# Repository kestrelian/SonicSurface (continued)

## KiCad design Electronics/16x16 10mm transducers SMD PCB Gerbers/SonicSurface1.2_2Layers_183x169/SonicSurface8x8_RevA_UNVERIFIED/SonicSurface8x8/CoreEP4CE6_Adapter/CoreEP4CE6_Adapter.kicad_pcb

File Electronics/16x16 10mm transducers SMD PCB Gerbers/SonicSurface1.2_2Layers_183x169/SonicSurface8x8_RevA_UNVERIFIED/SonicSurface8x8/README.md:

# SonicSurface 8x8 - Rev A

Local engineering design package, 22 October 2026. **UNVERIFIED: NOT RELEASED FOR FABRICATION.**

This is a new circuit and PCB implementation informed by the supplied SonicSurface manufacturing files. Gerbers do not preserve an editable schematic or authoritative circuit netlist. This package is not a recovered original KiCad project.

## Open in KiCad 10

- `Array8x8/Array8x8.kicad_pro`: 160 x 124 mm, two-layer array PCB; root schematic and eight row sheets.
- `CoreEP4CE6_Adapter/CoreEP4CE6_Adapter.kicad_pro`: 38 x 65 mm, two-layer plug-in P1-to-IDC26 cable adapter.
- Each project contains its own symbols, footprints and library tables.
- Each `fabrication_UNVERIFIED/` directory contains Gerber and Excellon exports. Do not send these to a manufacturer until the deferred checks pass.
- `schematic_svg/` contains readable schematic exports; `BOM.csv` lists components individually; `connectivity.csv` records intended pin-to-net assignments.
- `CABLE_PIN_MAP.csv` and `CoreEP4CE6_8x8_pins.qsf` define the module interface. `CHANNEL_MAP.csv` supplies all 64 physical and acoustic coordinates.
- `DESIGN_NOTES.md`, `ASSEMBLY.md`, and `QA_CHECKLIST.md` explain design assumptions, assembly, and deferred verification.

## Implemented parts

64 Murata MA40S4S; 32 Microchip TC4427EPA DIP-8; 8 74HC595N DIP-16. The driver package supersedes the earlier SOIC suggestion. The CoreEP4CE6 is external and connects through a straight 26-way ribbon and the adapter. No bare FPGA is fitted to the array.

The transducer pitch is **12 mm**, enlarged from the original approximately 10.5 mm to make room for DIP through-hole pads. The active grid spans 84 mm between the first and last centres. The transducer body envelope is about 94.2 x 94.2 mm at maximum body diameter. Array board area is about 35.8% smaller than the supplied 183 x 169 mm board.

## Completion and verification are separate

The package contains native editable design files and manufacturing exports. Routing generation status is recorded in each project's `routing_status.json`; that is an authoring log, **not** a connectivity, clearance, signal integrity or manufacturing test result. The array has routed ground connections supplemented by copper pours; the adapter has ground pours and stitching vias. The final checklist is intentionally unexecuted at the user's request. Physical fit, all-net connectivity, component ratings under actual operation, cable timing, and acoustic performance remain unverified.

No FPGA bitstream is supplied. The QSF is a pin-assignment fragment, not a complete Quartus project. Firmware adaptation and compilation are needed before use. The old 256-channel bitstream must not be used unchanged.

Everything remains local. Nothing has been committed, pushed, uploaded to a PCB service, or ordered.

## Reproduction

Use the Python supplied with KiCad 10. `build_design.py` regenerates placed boards and schematics, **overwriting edits in the generated project files**. Do not rebuild over manual work; copy the package first.

For the array, `prepare_router_input.py` produces a Specctra DSN with explicit 0.25 mm signal / 0.8 mm power / 0.4 mm ground rules. Route that DSN with Freerouting 2.5.0 Java locally, then run `import_array_routing.py` to import `authoring/routed.ses` and add ground pours. The session is included, so it can be re-imported without rerunning the router. `route_design.py CoreEP4CE6_Adapter` reproduces the adapter's grid routing. The grid router is retained for provenance but did not complete the array routing; do not replace the array with that intermediate result. `export_fabrication.py` writes Gerbers/drills from the native boards.

No script in this package runs the final QA checklist. The native Freerouting executable was blocked by Windows; the official Java distribution was used with a portable Temurin 25 runtime instead. Downloads and router runtime files are local under `tools/` but are excluded from the delivery ZIP. No Windows security setting was changed. The official tool and runtime can be obtained from [Freerouting releases](https://github.com/freerouting/freerouting/releases/tag/v2.5.0) and [Eclipse Adoptium](https://adoptium.net/).

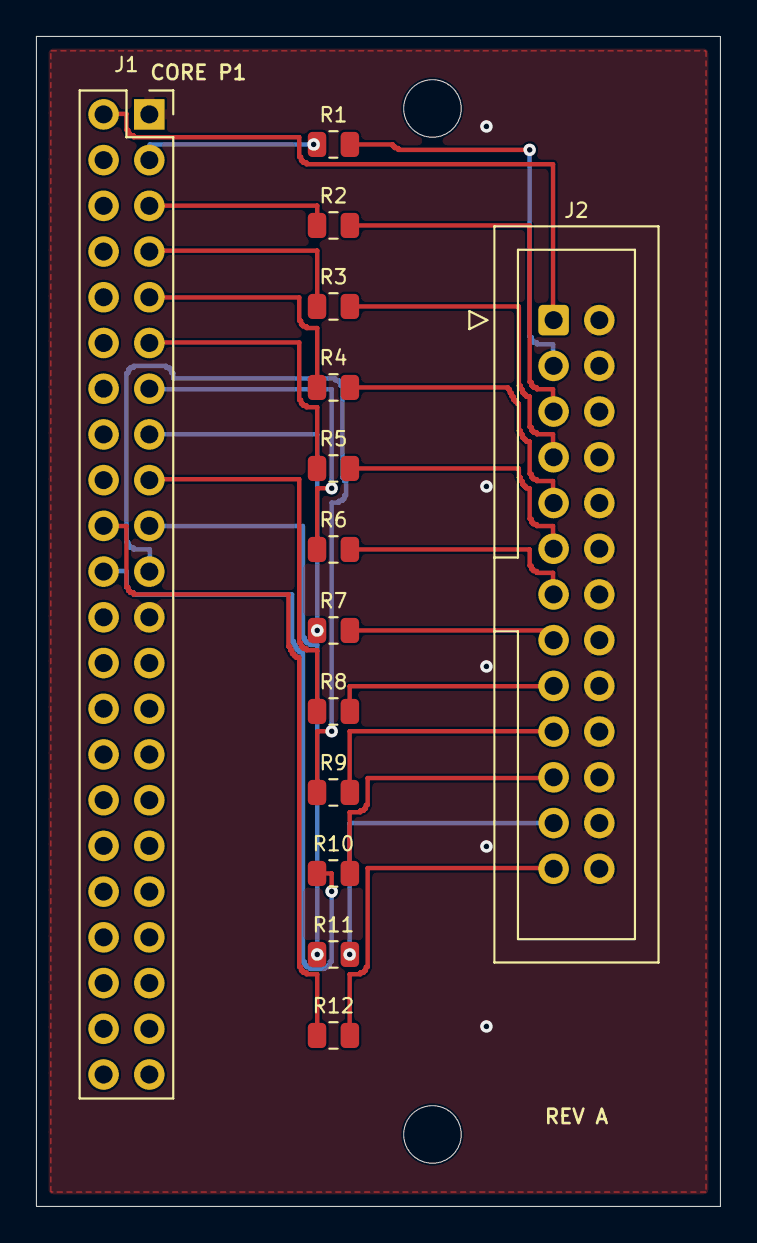
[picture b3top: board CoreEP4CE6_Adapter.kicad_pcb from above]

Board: 2 copper layers, 38.0 x 65.0 mm, 16 parts (0 on the bottom side), 26 nets.

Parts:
H1, H2: MountingHole_3.2mm_M3
J1: CoreEP4CE6 P1 ONLY; PinSocket_2x22_P2.54mm_Vertical
J2: IDC26 to ARRAY J1; IDC-Header_2x13_P2.54mm_Vertical
R1, R2, R3, R4, R5, R6, R7, R8, R9, R10, R11, R12: 33R source termination; R_0805_2012Metric

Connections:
+3V3: J1.2, J2.1
CLR_N: J2.25, R12.2
CLR_N_SRC: J1.20, R12.1
DATA0: J2.3, R1.2
DATA0_SRC: J1.3, R1.1
DATA1: J2.5, R2.2
DATA1_SRC: J1.5, R2.1
DATA2: J2.7, R3.2
DATA2_SRC: J1.7, R3.1
DATA3: J2.9, R4.2
DATA3_SRC: J1.9, R4.1
DATA4: J2.11, R5.2
DATA4_SRC: J1.11, R5.1
DATA5: J2.13, R6.2
DATA5_SRC: J1.13, R6.1
DATA6: J2.15, R7.2
DATA6_SRC: J1.15, R7.1
DATA7: J2.17, R8.2
DATA7_SRC: J1.17, R8.1
GND: J1.1, J1.23, J2.2, J2.4, J2.6, J2.8, J2.10, J2.12, J2.14, J2.16, J2.18, J2.20, J2.22, J2.24, J2.26
LATCH: J2.21, R10.2
LATCH_SRC: J1.22, R10.1
OE_N: J2.23, R11.2
OE_N_SRC: J1.19, R11.1
SCLK: J2.19, R9.2
SCLK_SRC: J1.21, R9.1

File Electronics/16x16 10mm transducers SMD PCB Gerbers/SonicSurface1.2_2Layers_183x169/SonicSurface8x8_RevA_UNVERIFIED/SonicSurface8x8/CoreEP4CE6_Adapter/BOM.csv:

Reference,Value / part,Footprint,Quantity,Notes
J1,CoreEP4CE6 P1 ONLY,SS8:PinSocket_2x22_P2.54mm_Vertical,1,Unverified Rev A
J2,IDC26 to ARRAY J1,SS8:IDC-Header_2x13_P2.54mm_Vertical,1,Unverified Rev A
R1,33R source termination,SS8:R_0805_2012Metric,1,Unverified Rev A
R2,33R source termination,SS8:R_0805_2012Metric,1,Unverified Rev A
R3,33R source termination,SS8:R_0805_2012Metric,1,Unverified Rev A
R4,33R source termination,SS8:R_0805_2012Metric,1,Unverified Rev A
R5,33R source termination,SS8:R_0805_2012Metric,1,Unverified Rev A
R6,33R source termination,SS8:R_0805_2012Metric,1,Unverified Rev A
R7,33R source termination,SS8:R_0805_2012Metric,1,Unverified Rev A
R8,33R source termination,SS8:R_0805_2012Metric,1,Unverified Rev A
R9,33R source termination,SS8:R_0805_2012Metric,1,Unverified Rev A
R10,33R source termination,SS8:R_0805_2012Metric,1,Unverified Rev A
R11,33R source termination,SS8:R_0805_2012Metric,1,Unverified Rev A
R12,33R source termination,SS8:R_0805_2012Metric,1,Unverified Rev A

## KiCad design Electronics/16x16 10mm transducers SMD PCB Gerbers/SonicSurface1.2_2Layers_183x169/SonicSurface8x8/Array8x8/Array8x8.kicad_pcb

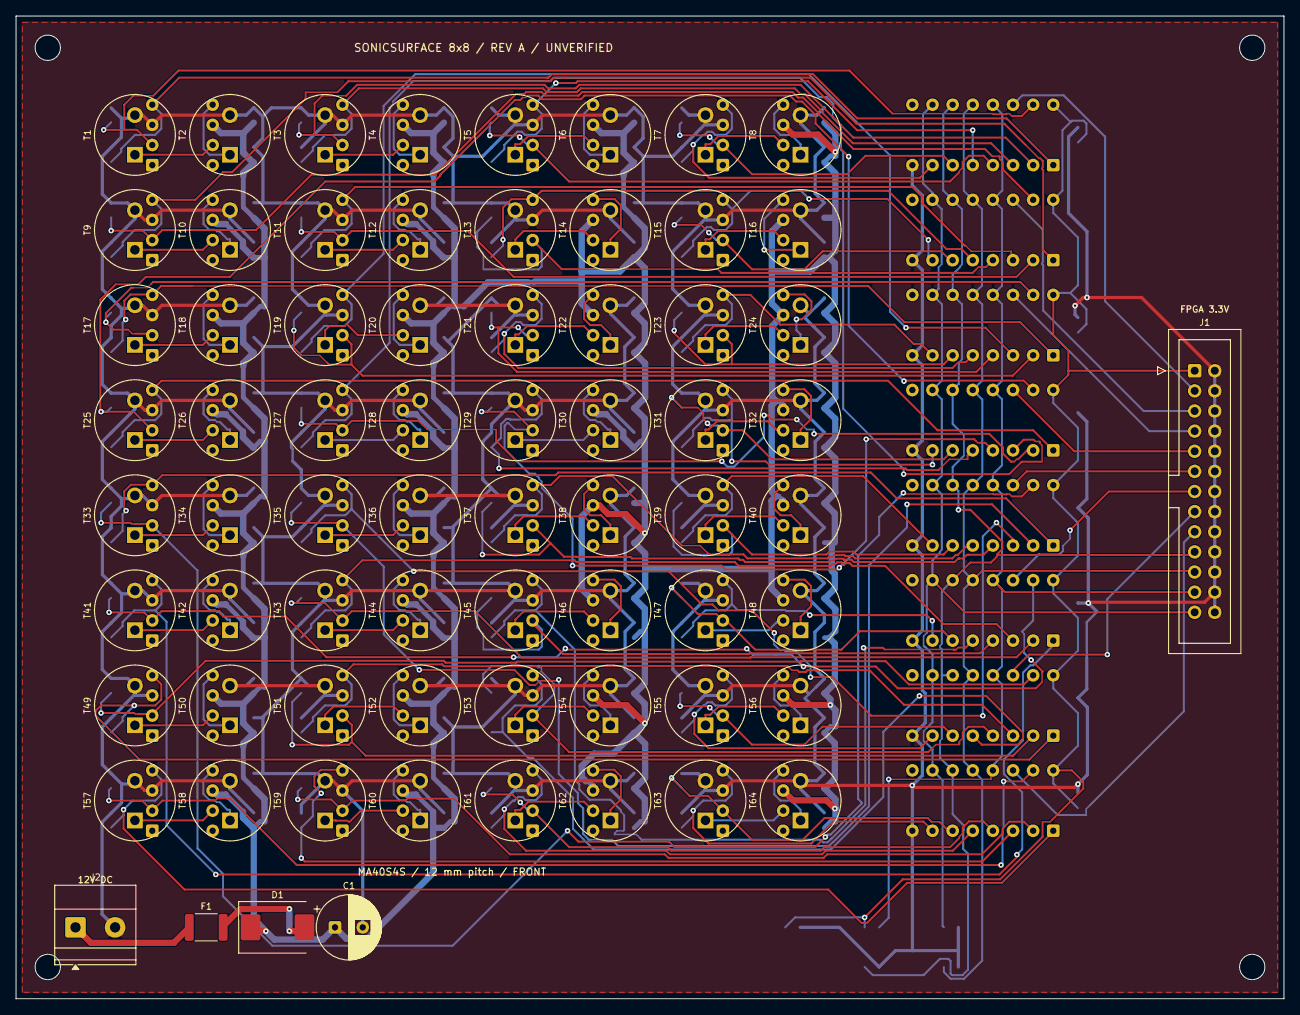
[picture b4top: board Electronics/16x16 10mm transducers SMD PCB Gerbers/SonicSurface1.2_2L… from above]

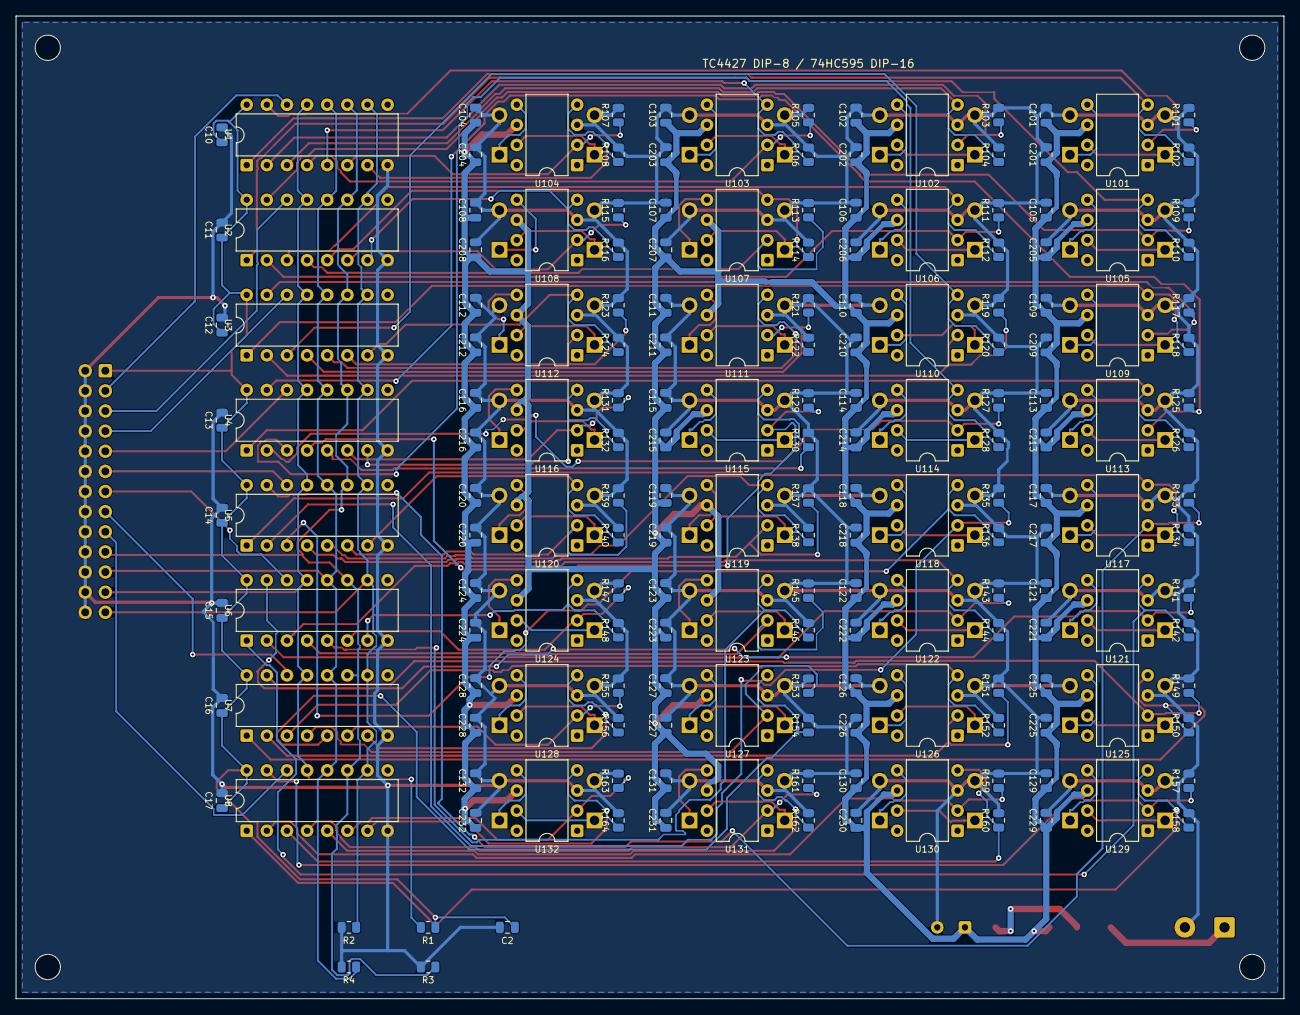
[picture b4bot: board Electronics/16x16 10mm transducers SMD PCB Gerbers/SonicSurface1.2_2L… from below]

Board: 2 copper layers, 160.0 x 124.0 mm, 254 parts (181 on the bottom side), 145 nets.

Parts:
C1: 220uF 35V low ESR; CP_Radial_D8.0mm_P3.50mm
C2: 10uF 10V X7R; C_0805_2012Metric
C10, C11, C12, C13, C14, C15, C16, C17, C101, C102, C103, C104, C105, C106, C107, C108, C109, C110, C111, C112, C113, C114, C115, C116, C117, C118, C119, C120, C121, C122, C123, C124, C125, C126, C127, C128, C129, C130, C131, C132: 100nF 50V X7R; C_0805_2012Metric
C201, C202, C203, C204, C205, C206, C207, C208, C209, C210, C211, C212, C213, C214, C215, C216, C217, C218, C219, C220, C221, C222, C223, C224, C225, C226, C227, C228, C229, C230, C231, C232: 1uF 50V X7R; C_0805_2012Metric
D1: SS34 / SMC; D_SMC
F1: 1A fast / 1812; Fuse_1812_4532Metric
H1, H2, H3, H4: MountingHole_3.2mm_M3
J1: IDC26 / FPGA CABLE; IDC-Header_2x13_P2.54mm_Vertical
J2: 12V DC INPUT; TerminalBlock_Phoenix_MKDS-1,5-2_1x02_P5.00mm_Horizontal
R1, R2, R3, R4, R101, R102, R103, R104, R105, R106, R107, R108, R109, R110, R111, R112, R113, R114, R115, R116, R117, R118, R119, R120, R121, R122, R123, R124, R125, R126, R127, R128, R129, R130, R131, R132, R133, R134, R135, R136, R137, R138, R139, R140, R141, R142, R143, R144, R145, R146, R147, R148, R149, R150, R151, R152, R153, R154, R155, R156, R157, R158, R159, R160, R161, R162, R163, R164: 10k; R_0805_2012Metric
T1, T2, T3, T4, T5, T6, T7, T8, T9, T10, T11, T12, T13, T14, T15, T16, T17, T18, T19, T20, T21, T22, T23, T24, T25, T26, T27, T28, T29, T30, T31, T32, T33, T34, T35, T36, T37, T38, T39, T40, T41, T42, T43, T44, T45, T46, T47, T48, T49, T50, T51, T52, T53, T54, T55, T56, T57, T58, T59, T60, T61, T62, T63, T64: MA40S4S; MA40S4S_P5mm
U1, U2, U3, U4, U5, U6, U7, U8: 74HC595N / DIP-16; DIP-16_W7.62mm
U101, U102, U103, U104, U105, U106, U107, U108, U109, U110, U111, U112, U113, U114, U115, U116, U117, U118, U119, U120, U121, U122, U123, U124, U125, U126, U127, U128, U129, U130, U131, U132: TC4427EPA / DIP-8; DIP-8_W7.62mm

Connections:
+3V3: C2.1, C10.1, C11.1, C12.1, C13.1, C14.1, C15.1, C16.1, C17.1, J1.1, R1.1, U1.16, U2.16, U3.16, U4.16, U5.16, U6.16, U7.16, U8.16
+12V: C1.1, C101.1, C102.1, C103.1, C104.1, C105.1, C106.1, C107.1, C108.1, C109.1, C110.1, C111.1, C112.1, C113.1, C114.1, C115.1, C116.1, C117.1, C118.1, C119.1, C120.1, C121.1, C122.1, C123.1, C124.1, C125.1, C126.1, C127.1, C128.1, C129.1, C130.1, C131.1, C132.1, C201.1, C202.1, C203.1, C204.1, C205.1, C206.1, C207.1, C208.1, C209.1, C210.1, C211.1, C212.1, C213.1, C214.1, C215.1, C216.1, C217.1, C218.1, C219.1, C220.1, C221.1, C222.1, C223.1, C224.1, C225.1, C226.1, C227.1, C228.1, C229.1, C230.1, C231.1, C232.1, D1.1, U101.6, U102.6, U103.6, U104.6, U105.6, U106.6, U107.6, U108.6, U109.6, U110.6, U111.6, U112.6, U113.6, U114.6, U115.6, U116.6, U117.6, U118.6, U119.6, U120.6, U121.6, U122.6, U123.6, U124.6, U125.6, U126.6, U127.6, U128.6, U129.6, U130.6, U131.6, U132.6
CLR_N: J1.25, R2.1, U1.10, U2.10, U3.10, U4.10, U5.10, U6.10, U7.10, U8.10
DATA0: J1.3, U1.14
DATA1: J1.5, U2.14
DATA2: J1.7, U3.14
DATA3: J1.9, U4.14
DATA4: J1.11, U5.14
DATA5: J1.13, U6.14
DATA6: J1.15, U7.14
DATA7: J1.17, U8.14
DRV00: T1.1, U101.7
DRV01: T2.1, U101.5
DRV02: T3.1, U102.7
DRV03: T4.1, U102.5
DRV04: T5.1, U103.7
DRV05: T6.1, U103.5
DRV06: T7.1, U104.7
DRV07: T8.1, U104.5
DRV08: T9.1, U105.7
DRV09: T10.1, U105.5
DRV10: T11.1, U106.7
DRV11: T12.1, U106.5
DRV12: T13.1, U107.7
DRV13: T14.1, U107.5
DRV14: T15.1, U108.7
DRV15: T16.1, U108.5
DRV16: T17.1, U109.7
DRV17: T18.1, U109.5
DRV18: T19.1, U110.7
DRV19: T20.1, U110.5
DRV20: T21.1, U111.7
DRV21: T22.1, U111.5
DRV22: T23.1, U112.7
DRV23: T24.1, U112.5
DRV24: T25.1, U113.7
DRV25: T26.1, U113.5
DRV26: T27.1, U114.7
DRV27: T28.1, U114.5
DRV28: T29.1, U115.7
DRV29: T30.1, U115.5
DRV30: T31.1, U116.7
DRV31: T32.1, U116.5
DRV32: T33.1, U117.7
DRV33: T34.1, U117.5
DRV34: T35.1, U118.7
DRV35: T36.1, U118.5
DRV36: T37.1, U119.7
DRV37: T38.1, U119.5
DRV38: T39.1, U120.7
DRV39: T40.1, U120.5
DRV40: T41.1, U121.7
DRV41: T42.1, U121.5
DRV42: T43.1, U122.7
DRV43: T44.1, U122.5
DRV44: T45.1, U123.7
DRV45: T46.1, U123.5
DRV46: T47.1, U124.7
DRV47: T48.1, U124.5
DRV48: T49.1, U125.7
DRV49: T50.1, U125.5
DRV50: T51.1, U126.7
DRV51: T52.1, U126.5
DRV52: T53.1, U127.7
DRV53: T54.1, U127.5
DRV54: T55.1, U128.7
DRV55: T56.1, U128.5
DRV56: T57.1, U129.7
DRV57: T58.1, U129.5
DRV58: T59.1, U130.7
DRV59: T60.1, U130.5
DRV60: T61.1, U131.7
DRV61: T62.1, U131.5
DRV62: T63.1, U132.7
DRV63: T64.1, U132.5
GND: C1.2, C2.2, C10.2, C11.2, C12.2, C13.2, C14.2, C15.2, C16.2, C17.2, C101.2, C102.2, C103.2, C104.2, C105.2, C106.2, C107.2, C108.2, C109.2, C110.2, C111.2, C112.2, C113.2, C114.2, C115.2, C116.2, C117.2, C118.2, C119.2, C120.2, C121.2, C122.2, C123.2, C124.2, C125.2, C126.2, C127.2, C128.2, C129.2, C130.2, C131.2, C132.2, C201.2, C202.2, C203.2, C204.2, C205.2, C206.2, C207.2, C208.2, C209.2, C210.2, C211.2, C212.2, C213.2, C214.2, C215.2, C216.2, C217.2, C218.2, C219.2, C220.2, C221.2, C222.2, C223.2, C224.2, C225.2, C226.2, C227.2, C228.2, C229.2, C230.2, C231.2, C232.2, J1.2, J1.4, J1.6, J1.8, J1.10, J1.12, J1.14, J1.16, J1.18, J1.20, J1.22, J1.24, J1.26, J2.2, R2.2, R3.2, R4.2, R101.2, R102.2, R103.2, R104.2, R105.2, R106.2, R107.2, R108.2, R109.2, R110.2, R111.2, R112.2, R113.2, R114.2, R115.2, R116.2, R117.2, R118.2, R119.2, R120.2, R121.2, R122.2, R123.2, R124.2, R125.2, R126.2, R127.2, R128.2, R129.2, R130.2, R131.2, R132.2, R133.2, R134.2, R135.2, R136.2, R137.2, R138.2, R139.2, R140.2, R141.2, R142.2, R143.2, R144.2, R145.2, R146.2, R147.2, R148.2, R149.2, R150.2, R151.2, R152.2, R153.2, R154.2, R155.2, R156.2, R157.2, R158.2, R159.2, R160.2, R161.2, R162.2, R163.2, R164.2, T1.2, T2.2, T3.2, T4.2, T5.2, T6.2, T7.2, T8.2, T9.2, T10.2, T11.2, T12.2, T13.2, T14.2, T15.2, T16.2, T17.2, T18.2, T19.2, T20.2, T21.2, T22.2, T23.2, T24.2, T25.2, T26.2, T27.2, T28.2, T29.2, T30.2, T31.2, T32.2, T33.2, T34.2, T35.2, T36.2, T37.2, T38.2, T39.2, T40.2, T41.2, T42.2, T43.2, T44.2, T45.2, T46.2, T47.2, T48.2, T49.2, T50.2, T51.2, T52.2, T53.2, T54.2, T55.2, T56.2, T57.2, T58.2, T59.2, T60.2, T61.2, T62.2, T63.2, T64.2, U1.8, U2.8, U3.8, U4.8, U5.8, U6.8, U7.8, U8.8, U101.3, U102.3, U103.3, U104.3, U105.3, U106.3, U107.3, U108.3, U109.3, U110.3, U111.3, U112.3, U113.3, U114.3, U115.3, U116.3, U117.3, U118.3, U119.3, U120.3, U121.3, U122.3, U123.3, U124.3, U125.3, U126.3, U127.3, U128.3, U129.3, U130.3, U131.3, U132.3
LATCH: J1.21, R4.1, U1.12, U2.12, U3.12, U4.12, U5.12, U6.12, U7.12, U8.12
OE_N: J1.23, R1.2, U1.13, U2.13, U3.13, U4.13, U5.13, U6.13, U7.13, U8.13
Q00: R101.1, U1.15, U101.2
Q01: R102.1, U1.1, U101.4
Q02: R103.1, U1.2, U102.2
Q03: R104.1, U1.3, U102.4
Q04: R105.1, U1.4, U103.2
Q05: R106.1, U1.5, U103.4
Q06: R107.1, U1.6, U104.2
Q07: R108.1, U1.7, U104.4
Q08: R109.1, U2.15, U105.2
Q09: R110.1, U2.1, U105.4
Q10: R111.1, U2.2, U106.2
Q11: R112.1, U2.3, U106.4
Q12: R113.1, U2.4, U107.2
Q13: R114.1, U2.5, U107.4
Q14: R115.1, U2.6, U108.2
Q15: R116.1, U2.7, U108.4
Q16: R117.1, U3.15, U109.2
Q17: R118.1, U3.1, U109.4
Q18: R119.1, U3.2, U110.2
Q19: R120.1, U3.3, U110.4
Q20: R121.1, U3.4, U111.2
Q21: R122.1, U3.5, U111.4
Q22: R123.1, U3.6, U112.2
Q23: R124.1, U3.7, U112.4
Q24: R125.1, U4.15, U113.2
Q25: R126.1, U4.1, U113.4
Q26: R127.1, U4.2, U114.2
Q27: R128.1, U4.3, U114.4
Q28: R129.1, U4.4, U115.2
Q29: R130.1, U4.5, U115.4
Q30: R131.1, U4.6, U116.2
Q31: R132.1, U4.7, U116.4
Q32: R133.1, U5.15, U117.2
Q33: R134.1, U5.1, U117.4
Q34: R135.1, U5.2, U118.2
Q35: R136.1, U5.3, U118.4
Q36: R137.1, U5.4, U119.2
Q37: R138.1, U5.5, U119.4
Q38: R139.1, U5.6, U120.2
Q39: R140.1, U5.7, U120.4
Q40: R141.1, U6.15, U121.2
Q41: R142.1, U6.1, U121.4
Q42: R143.1, U6.2, U122.2
Q43: R144.1, U6.3, U122.4
Q44: R145.1, U6.4, U123.2
Q45: R146.1, U6.5, U123.4
Q46: R147.1, U6.6, U124.2
Q47: R148.1, U6.7, U124.4
Q48: R149.1, U7.15, U125.2
Q49: R150.1, U7.1, U125.4
Q50: R151.1, U7.2, U126.2
Q51: R152.1, U7.3, U126.4
Q52: R153.1, U7.4, U127.2
Q53: R154.1, U7.5, U127.4
Q54: R155.1, U7.6, U128.2
Q55: R156.1, U7.7, U128.4
Q56: R157.1, U8.15, U129.2
Q57: R158.1, U8.1, U129.4
Q58: R159.1, U8.2, U130.2
Q59: R160.1, U8.3, U130.4
Q60: R161.1, U8.4, U131.2
Q61: R162.1, U8.5, U131.4
Q62: R163.1, U8.6, U132.2
Q63: R164.1, U8.7, U132.4
SCLK: J1.19, R3.1, U1.11, U2.11, U3.11, U4.11, U5.11, U6.11, U7.11, U8.11
VFUSED: D1.2, F1.2
VIN: F1.1, J2.1

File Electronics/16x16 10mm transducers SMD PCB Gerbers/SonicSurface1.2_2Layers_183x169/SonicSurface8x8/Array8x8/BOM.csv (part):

Reference,Value / part,Footprint,Quantity,Notes
J1,IDC26 / FPGA CABLE,SS8:IDC-Header_2x13_P2.54mm_Vertical,1,Unverified Rev A
J2,12V DC INPUT,"SS8:TerminalBlock_Phoenix_MKDS-1,5-2_1x02_P5.00mm_Horizontal",1,Unverified Rev A
F1,1A fast / 1812,SS8:Fuse_1812_4532Metric,1,Unverified Rev A
D1,SS34 / SMC,SS8:D_SMC,1,Unverified Rev A
C1,220uF 35V low ESR,SS8:CP_Radial_D8.0mm_P3.50mm,1,Unverified Rev A
C2,10uF 10V X7R,SS8:C_0805_2012Metric,1,Unverified Rev A
R1,10k,SS8:R_0805_2012Metric,1,Unverified Rev A
R2,10k,SS8:R_0805_2012Metric,1,Unverified Rev A
R3,10k,SS8:R_0805_2012Metric,1,Unverified Rev A
R4,10k,SS8:R_0805_2012Metric,1,Unverified Rev A
U1,74HC595N / DIP-16,SS8:DIP-16_W7.62mm,1,Unverified Rev A
C10,100nF 50V X7R,SS8:C_0805_2012Metric,1,Unverified Rev A
U101,TC4427EPA / DIP-8,SS8:DIP-8_W7.62mm,1,Unverified Rev A
C101,100nF 50V X7R,SS8:C_0805_2012Metric,1,Unverified Rev A
C201,1uF 50V X7R,SS8:C_0805_2012Metric,1,Unverified Rev A
R101,10k,SS8:R_0805_2012Metric,1,Unverified Rev A
T1,MA40S4S,SS8:MA40S4S_P5mm,1,Unverified Rev A
R102,10k,SS8:R_0805_2012Metric,1,Unverified Rev A
T2,MA40S4S,SS8:MA40S4S_P5mm,1,Unverified Rev A
U102,TC4427EPA / DIP-8,SS8:DIP-8_W7.62mm,1,Unverified Rev A
C102,100nF 50V X7R,SS8:C_0805_2012Metric,1,Unverified Rev A
C202,1uF 50V X7R,SS8:C_0805_2012Metric,1,Unverified Rev A
R103,10k,SS8:R_0805_2012Metric,1,Unverified Rev A
T3,MA40S4S,SS8:MA40S4S_P5mm,1,Unverified Rev A
R104,10k,SS8:R_0805_2012Metric,1,Unverified Rev A
T4,MA40S4S,SS8:MA40S4S_P5mm,1,Unverified Rev A
U103,TC4427EPA / DIP-8,SS8:DIP-8_W7.62mm,1,Unverified Rev A
C103,100nF 50V X7R,SS8:C_0805_2012Metric,1,Unverified Rev A
C203,1uF 50V X7R,SS8:C_0805_2012Metric,1,Unverified Rev A
R105,10k,SS8:R_0805_2012Metric,1,Unverified Rev A
T5,MA40S4S,SS8:MA40S4S_P5mm,1,Unverified Rev A
R106,10k,SS8:R_0805_2012Metric,1,Unverified Rev A
T6,MA40S4S,SS8:MA40S4S_P5mm,1,Unverified Rev A
U104,TC4427EPA / DIP-8,SS8:DIP-8_W7.62mm,1,Unverified Rev A
C104,100nF 50V X7R,SS8:C_0805_2012Metric,1,Unverified Rev A
C204,1uF 50V X7R,SS8:C_0805_2012Metric,1,Unverified Rev A
R107,10k,SS8:R_0805_2012Metric,1,Unverified Rev A
T7,MA40S4S,SS8:MA40S4S_P5mm,1,Unverified Rev A
R108,10k,SS8:R_0805_2012Metric,1,Unverified Rev A
T8,MA40S4S,SS8:MA40S4S_P5mm,1,Unverified Rev A
U2,74HC595N / DIP-16,SS8:DIP-16_W7.62mm,1,Unverified Rev A
C11,100nF 50V X7R,SS8:C_0805_2012Metric,1,Unverified Rev A
U105,TC4427EPA / DIP-8,SS8:DIP-8_W7.62mm,1,Unverified Rev A
C105,100nF 50V X7R,SS8:C_0805_2012Metric,1,Unverified Rev A
C205,1uF 50V X7R,SS8:C_0805_2012Metric,1,Unverified Rev A
R109,10k,SS8:R_0805_2012Metric,1,Unverified Rev A
T9,MA40S4S,SS8:MA40S4S_P5mm,1,Unverified Rev A
R110,10k,SS8:R_0805_2012Metric,1,Unverified Rev A
T10,MA40S4S,SS8:MA40S4S_P5mm,1,Unverified Rev A
U106,TC4427EPA / DIP-8,SS8:DIP-8_W7.62mm,1,Unverified Rev A
C106,100nF 50V X7R,SS8:C_0805_2012Metric,1,Unverified Rev A
C206,1uF 50V X7R,SS8:C_0805_2012Metric,1,Unverified Rev A
R111,10k,SS8:R_0805_2012Metric,1,Unverified Rev A
T11,MA40S4S,SS8:MA40S4S_P5mm,1,Unverified Rev A
R112,10k,SS8:R_0805_2012Metric,1,Unverified Rev A
T12,MA40S4S,SS8:MA40S4S_P5mm,1,Unverified Rev A
U107,TC4427EPA / DIP-8,SS8:DIP-8_W7.62mm,1,Unverified Rev A
C107,100nF 50V X7R,SS8:C_0805_2012Metric,1,Unverified Rev A
C207,1uF 50V X7R,SS8:C_0805_2012Metric,1,Unverified Rev A
R113,10k,SS8:R_0805_2012Metric,1,Unverified Rev A
T13,MA40S4S,SS8:MA40S4S_P5mm,1,Unverified Rev A
R114,10k,SS8:R_0805_2012Metric,1,Unverified Rev A
T14,MA40S4S,SS8:MA40S4S_P5mm,1,Unverified Rev A
U108,TC4427EPA / DIP-8,SS8:DIP-8_W7.62mm,1,Unverified Rev A
C108,100nF 50V X7R,SS8:C_0805_2012Metric,1,Unverified Rev A
C208,1uF 50V X7R,SS8:C_0805_2012Metric,1,Unverified Rev A
R115,10k,SS8:R_0805_2012Metric,1,Unverified Rev A
T15,MA40S4S,SS8:MA40S4S_P5mm,1,Unverified Rev A
R116,10k,SS8:R_0805_2012Metric,1,Unverified Rev A
T16,MA40S4S,SS8:MA40S4S_P5mm,1,Unverified Rev A
U3,74HC595N / DIP-16,SS8:DIP-16_W7.62mm,1,Unverified Rev A
C12,100nF 50V X7R,SS8:C_0805_2012Metric,1,Unverified Rev A
U109,TC4427EPA / DIP-8,SS8:DIP-8_W7.62mm,1,Unverified Rev A
C109,100nF 50V X7R,SS8:C_0805_2012Metric,1,Unverified Rev A
C209,1uF 50V X7R,SS8:C_0805_2012Metric,1,Unverified Rev A
R117,10k,SS8:R_0805_2012Metric,1,Unverified Rev A
T17,MA40S4S,SS8:MA40S4S_P5mm,1,Unverified Rev A
R118,10k,SS8:R_0805_2012Metric,1,Unverified Rev A
T18,MA40S4S,SS8:MA40S4S_P5mm,1,Unverified Rev A
U110,TC4427EPA / DIP-8,SS8:DIP-8_W7.62mm,1,Unverified Rev A
C110,100nF 50V X7R,SS8:C_0805_2012Metric,1,Unverified Rev A
C210,1uF 50V X7R,SS8:C_0805_2012Metric,1,Unverified Rev A
R119,10k,SS8:R_0805_2012Metric,1,Unverified Rev A
T19,MA40S4S,SS8:MA40S4S_P5mm,1,Unverified Rev A
R120,10k,SS8:R_0805_2012Metric,1,Unverified Rev A
T20,MA40S4S,SS8:MA40S4S_P5mm,1,Unverified Rev A
U111,TC4427EPA / DIP-8,SS8:DIP-8_W7.62mm,1,Unverified Rev A
C111,100nF 50V X7R,SS8:C_0805_2012Metric,1,Unverified Rev A
C211,1uF 50V X7R,SS8:C_0805_2012Metric,1,Unverified Rev A
R121,10k,SS8:R_0805_2012Metric,1,Unverified Rev A
T21,MA40S4S,SS8:MA40S4S_P5mm,1,Unverified Rev A
R122,10k,SS8:R_0805_2012Metric,1,Unverified Rev A
T22,MA40S4S,SS8:MA40S4S_P5mm,1,Unverified Rev A
U112,TC4427EPA / DIP-8,SS8:DIP-8_W7.62mm,1,Unverified Rev A
C112,100nF 50V X7R,SS8:C_0805_2012Metric,1,Unverified Rev A
C212,1uF 50V X7R,SS8:C_0805_2012Metric,1,Unverified Rev A
R123,10k,SS8:R_0805_2012Metric,1,Unverified Rev A
T23,MA40S4S,SS8:MA40S4S_P5mm,1,Unverified Rev A
R124,10k,SS8:R_0805_2012Metric,1,Unverified Rev A
T24,MA40S4S,SS8:MA40S4S_P5mm,1,Unverified Rev A
U4,74HC595N / DIP-16,SS8:DIP-16_W7.62mm,1,Unverified Rev A
C13,100nF 50V X7R,SS8:C_0805_2012Metric,1,Unverified Rev A
U113,TC4427EPA / DIP-8,SS8:DIP-8_W7.62mm,1,Unverified Rev A
C113,100nF 50V X7R,SS8:C_0805_2012Metric,1,Unverified Rev A
C213,1uF 50V X7R,SS8:C_0805_2012Metric,1,Unverified Rev A
R125,10k,SS8:R_0805_2012Metric,1,Unverified Rev A
T25,MA40S4S,SS8:MA40S4S_P5mm,1,Unverified Rev A
R126,10k,SS8:R_0805_2012Metric,1,Unverified Rev A
T26,MA40S4S,SS8:MA40S4S_P5mm,1,Unverified Rev A
U114,TC4427EPA / DIP-8,SS8:DIP-8_W7.62mm,1,Unverified Rev A
C114,100nF 50V X7R,SS8:C_0805_2012Metric,1,Unverified Rev A
C214,1uF 50V X7R,SS8:C_0805_2012Metric,1,Unverified Rev A
R127,10k,SS8:R_0805_2012Metric,1,Unverified Rev A
T27,MA40S4S,SS8:MA40S4S_P5mm,1,Unverified Rev A
R128,10k,SS8:R_0805_2012Metric,1,Unverified Rev A
T28,MA40S4S,SS8:MA40S4S_P5mm,1,Unverified Rev A
U115,TC4427EPA / DIP-8,SS8:DIP-8_W7.62mm,1,Unverified Rev A
C115,100nF 50V X7R,SS8:C_0805_2012Metric,1,Unverified Rev A
C215,1uF 50V X7R,SS8:C_0805_2012Metric,1,Unverified Rev A
R129,10k,SS8:R_0805_2012Metric,1,Unverified Rev A
T29,MA40S4S,SS8:MA40S4S_P5mm,1,Unverified Rev A
R130,10k,SS8:R_0805_2012Metric,1,Unverified Rev A
T30,MA40S4S,SS8:MA40S4S_P5mm,1,Unverified Rev A
U116,TC4427EPA / DIP-8,SS8:DIP-8_W7.62mm,1,Unverified Rev A
C116,100nF 50V X7R,SS8:C_0805_2012Metric,1,Unverified Rev A
C216,1uF 50V X7R,SS8:C_0805_2012Metric,1,Unverified Rev A
R131,10k,SS8:R_0805_2012Metric,1,Unverified Rev A
T31,MA40S4S,SS8:MA40S4S_P5mm,1,Unverified Rev A
R132,10k,SS8:R_0805_2012Metric,1,Unverified Rev A
T32,MA40S4S,SS8:MA40S4S_P5mm,1,Unverified Rev A
U5,74HC595N / DIP-16,SS8:DIP-16_W7.62mm,1,Unverified Rev A
C14,100nF 50V X7R,SS8:C_0805_2012Metric,1,Unverified Rev A
U117,TC4427EPA / DIP-8,SS8:DIP-8_W7.62mm,1,Unverified Rev A
C117,100nF 50V X7R,SS8:C_0805_2012Metric,1,Unverified Rev A
C217,1uF 50V X7R,SS8:C_0805_2012Metric,1,Unverified Rev A
R133,10k,SS8:R_0805_2012Metric,1,Unverified Rev A
T33,MA40S4S,SS8:MA40S4S_P5mm,1,Unverified Rev A
R134,10k,SS8:R_0805_2012Metric,1,Unverified Rev A
T34,MA40S4S,SS8:MA40S4S_P5mm,1,Unverified Rev A
U118,TC4427EPA / DIP-8,SS8:DIP-8_W7.62mm,1,Unverified Rev A
C118,100nF 50V X7R,SS8:C_0805_2012Metric,1,Unverified Rev A
C218,1uF 50V X7R,SS8:C_0805_2012Metric,1,Unverified Rev A
R135,10k,SS8:R_0805_2012Metric,1,Unverified Rev A
T35,MA40S4S,SS8:MA40S4S_P5mm,1,Unverified Rev A
R136,10k,SS8:R_0805_2012Metric,1,Unverified Rev A
T36,MA40S4S,SS8:MA40S4S_P5mm,1,Unverified Rev A
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
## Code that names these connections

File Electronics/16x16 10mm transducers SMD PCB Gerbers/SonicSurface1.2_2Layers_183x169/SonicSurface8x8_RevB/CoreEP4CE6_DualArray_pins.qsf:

# Hardware interface only. No firmware or bitstream supplied.
set_global_assignment -name FAMILY "Cyclone IV E"
set_global_assignment -name DEVICE EP4CE6E22C8
set_location_assignment PIN_23 -to CLK_50
set_instance_assignment -name IO_STANDARD "3.3-V LVTTL" -to CLK_50
set_location_assignment PIN_59 -to {A_DATA[0]}
set_instance_assignment -name IO_STANDARD "3.3-V LVTTL" -to {A_DATA[0]}
set_location_assignment PIN_64 -to {A_DATA[1]}
set_instance_assignment -name IO_STANDARD "3.3-V LVTTL" -to {A_DATA[1]}
set_location_assignment PIN_66 -to {A_DATA[2]}
set_instance_assignment -name IO_STANDARD "3.3-V LVTTL" -to {A_DATA[2]}
set_location_assignment PIN_68 -to {A_DATA[3]}
set_instance_assignment -name IO_STANDARD "3.3-V LVTTL" -to {A_DATA[3]}
set_location_assignment PIN_70 -to {A_DATA[4]}
set_instance_assignment -name IO_STANDARD "3.3-V LVTTL" -to {A_DATA[4]}
set_location_assignment PIN_72 -to {A_DATA[5]}
set_instance_assignment -name IO_STANDARD "3.3-V LVTTL" -to {A_DATA[5]}
set_location_assignment PIN_74 -to {A_DATA[6]}
set_instance_assignment -name IO_STANDARD "3.3-V LVTTL" -to {A_DATA[6]}
set_location_assignment PIN_76 -to {A_DATA[7]}
set_instance_assignment -name IO_STANDARD "3.3-V LVTTL" -to {A_DATA[7]}
set_location_assignment PIN_60 -to {B_DATA[0]}
set_instance_assignment -name IO_STANDARD "3.3-V LVTTL" -to {B_DATA[0]}
set_location_assignment PIN_65 -to {B_DATA[1]}
set_instance_assignment -name IO_STANDARD "3.3-V LVTTL" -to {B_DATA[1]}
set_location_assignment PIN_67 -to {B_DATA[2]}
set_instance_assignment -name IO_STANDARD "3.3-V LVTTL" -to {B_DATA[2]}
set_location_assignment PIN_69 -to {B_DATA[3]}
set_instance_assignment -name IO_STANDARD "3.3-V LVTTL" -to {B_DATA[3]}
set_location_assignment PIN_71 -to {B_DATA[4]}
set_instance_assignment -name IO_STANDARD "3.3-V LVTTL" -to {B_DATA[4]}
set_location_assignment PIN_73 -to {B_DATA[5]}
set_instance_assignment -name IO_STANDARD "3.3-V LVTTL" -to {B_DATA[5]}
set_location_assignment PIN_75 -to {B_DATA[6]}
set_instance_assignment -name IO_STANDARD "3.3-V LVTTL" -to {B_DATA[6]}
set_location_assignment PIN_77 -to {B_DATA[7]}
set_instance_assignment -name IO_STANDARD "3.3-V LVTTL" -to {B_DATA[7]}
set_location_assignment PIN_84 -to {SCLK}
set_instance_assignment -name IO_STANDARD "3.3-V LVTTL" -to {SCLK}
set_location_assignment PIN_85 -to {LATCH}
set_instance_assignment -name IO_STANDARD "3.3-V LVTTL" -to {LATCH}
set_location_assignment PIN_80 -to {A_OE_N}
set_instance_assignment -name IO_STANDARD "3.3-V LVTTL" -to {A_OE_N}
set_location_assignment PIN_83 -to {B_OE_N}
set_instance_assignment -name IO_STANDARD "3.3-V LVTTL" -to {B_OE_N}
set_location_assignment PIN_86 -to {A_CLR_N}
set_instance_assignment -name IO_STANDARD "3.3-V LVTTL" -to {A_CLR_N}
set_location_assignment PIN_87 -to {B_CLR_N}
set_instance_assignment -name IO_STANDARD "3.3-V LVTTL" -to {B_CLR_N}

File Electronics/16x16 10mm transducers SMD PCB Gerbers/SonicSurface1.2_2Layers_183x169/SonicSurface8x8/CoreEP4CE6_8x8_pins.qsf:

# Rev A pin assignments only; integrate with a 64-channel HDL project.
set_global_assignment -name FAMILY "Cyclone IV E"
set_global_assignment -name DEVICE EP4CE6E22C8
set_location_assignment PIN_23 -to CLK_50
set_instance_assignment -name IO_STANDARD "3.3-V LVTTL" -to CLK_50
set_location_assignment PIN_59 -to DATA[0]
set_instance_assignment -name IO_STANDARD "3.3-V LVTTL" -to DATA[0]
set_location_assignment PIN_64 -to DATA[1]
set_instance_assignment -name IO_STANDARD "3.3-V LVTTL" -to DATA[1]
set_location_assignment PIN_66 -to DATA[2]
set_instance_assignment -name IO_STANDARD "3.3-V LVTTL" -to DATA[2]
set_location_assignment PIN_68 -to DATA[3]
set_instance_assignment -name IO_STANDARD "3.3-V LVTTL" -to DATA[3]
set_location_assignment PIN_70 -to DATA[4]
set_instance_assignment -name IO_STANDARD "3.3-V LVTTL" -to DATA[4]
set_location_assignment PIN_72 -to DATA[5]
set_instance_assignment -name IO_STANDARD "3.3-V LVTTL" -to DATA[5]
set_location_assignment PIN_74 -to DATA[6]
set_instance_assignment -name IO_STANDARD "3.3-V LVTTL" -to DATA[6]
set_location_assignment PIN_76 -to DATA[7]
set_instance_assignment -name IO_STANDARD "3.3-V LVTTL" -to DATA[7]
set_location_assignment PIN_84 -to SCLK
set_instance_assignment -name IO_STANDARD "3.3-V LVTTL" -to SCLK
set_location_assignment PIN_85 -to LATCH
set_instance_assignment -name IO_STANDARD "3.3-V LVTTL" -to LATCH
set_location_assignment PIN_80 -to OE_N
set_instance_assignment -name IO_STANDARD "3.3-V LVTTL" -to OE_N
set_location_assignment PIN_83 -to CLR_N
set_instance_assignment -name IO_STANDARD "3.3-V LVTTL" -to CLR_N
